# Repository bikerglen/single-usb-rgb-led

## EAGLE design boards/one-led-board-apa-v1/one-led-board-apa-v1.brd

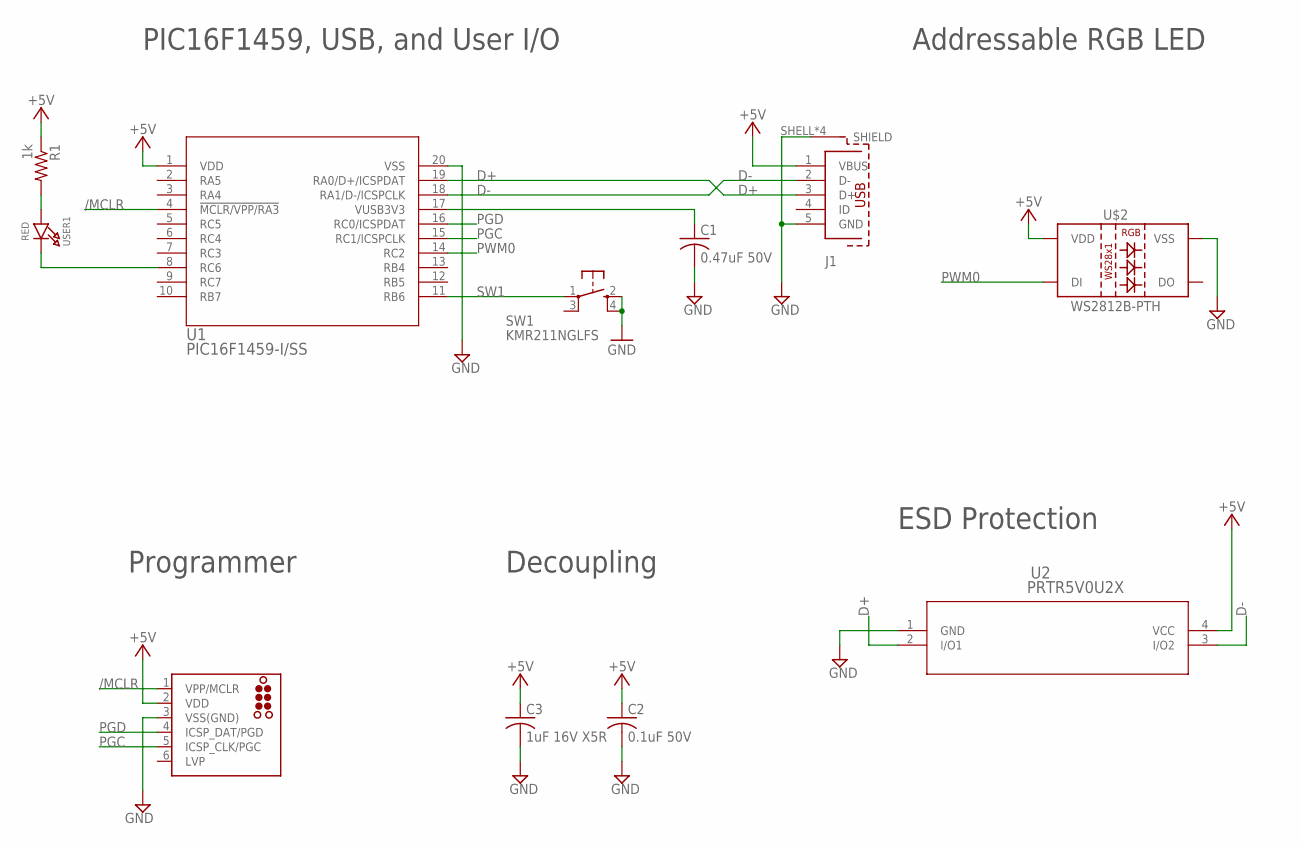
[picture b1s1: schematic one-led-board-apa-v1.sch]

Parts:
C1: 0.47uF 50V; C1206K; MFR_PART_NO C1206C474K5RACTU
C2: 0.1uF 50V; C1206K; MFR_PART_NO C1206S104M5RACTU
C3: 1uF 16V X5R; C1210; MFR_PART_NO C1210C105K4PACTU
J1: 629105136821
J3: TC2030-MCP-NL
R1: 1k; R0805
SW1: KMR211NGLFS; KMR2
U1: PIC16F1459-I/SS; SSOP20_MC
U2: PRTR5V0U2X; SOT143B
U$2: WS2812B-PTH; WS2812B-PTH-KIT
USER1: RED; CHIPLED_0805_NOOUTLINE

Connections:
+5V: C2.1, C3.1, J1.1 (VBUS), J3.2 (VDD), R1.1, U1.1 (VDD), U2.4 (VCC), U$2.2 (VDD)
/MCLR: J3.1 (VPP/MCLR), U1.4 (!MCLR/VPP/RA3)
D+: J1.3 (D+), U1.19 (RA0/D+/ICSPDAT), U2.2 (I/O1)
D-: J1.2 (D-), U1.18 (RA1/D-/ICSPCLK), U2.3 (I/O2)
GND: C1.2, C2.2, C3.2, J1.5 (GND), J1.SHELL (SHIELD), J1.SHELL1 (SHIELD), J1.SHELL2 (SHIELD), J1.SHELL3 (SHIELD), J3.3 (VSS(GND)), SW1.2 (S), SW1.4 (S1), U1.20 (VSS), U2.1 (GND), U$2.3 (VSS)
unnamed: R1.2, USER1.A
unnamed: U1.8 (RC6), USER1.C
PGC: J3.5 (ICSP_CLK/PGC), U1.15 (RC1/ICSPCLK)
PGD: J3.4 (ICSP_DAT/PGD), U1.16 (RC0/ICSPDAT)
PWM0: U1.14 (RC2), U$2.1 (DI)
SW1: SW1.1, U1.11 (RB6)
VUSB: C1.1, U1.17 (VUSB3V3)

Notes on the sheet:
PIC16F1459, USB, and User I/O
Addressable RGB LED
Programmer
Decoupling
ESD Protection

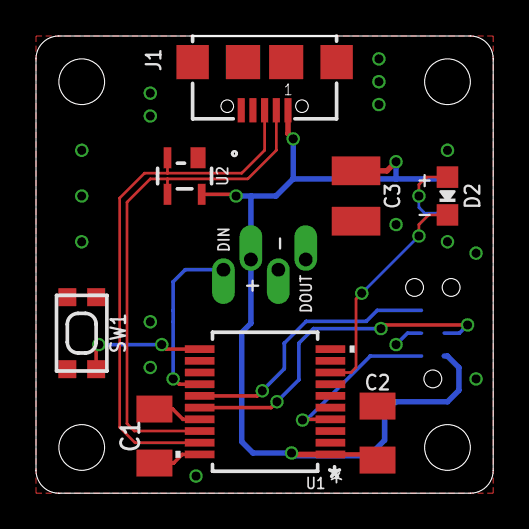
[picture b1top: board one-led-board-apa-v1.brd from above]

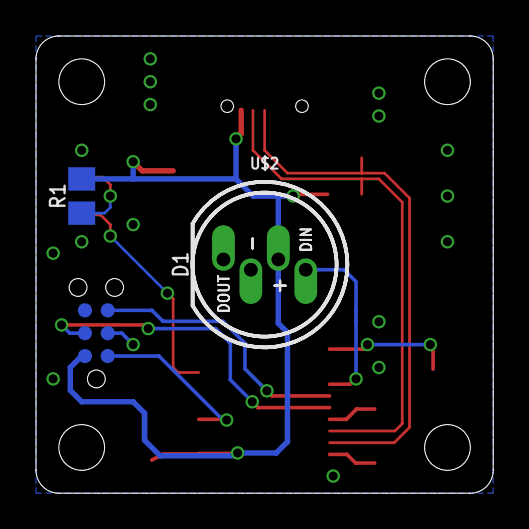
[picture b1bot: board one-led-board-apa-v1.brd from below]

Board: 2 copper layers, 25.4 x 25.4 mm, 11 parts (3 on the bottom side), 12 nets.

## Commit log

2020-06-29 initial checkin of boards
2020-06-29 initial checkin of enclosure
2021-11-02 add software directory

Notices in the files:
parts and their libraries:
InputOutputIO: Copyright: Würth Elektronik
tag-connect: ©2009 ROFA.cz - modified and updated by Robert Darlington ‹rdarlington@gmail.com›
microbuilder: This work is placed in the public domain, and may be freely used for commercial and non-commercial work with the following conditions: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
